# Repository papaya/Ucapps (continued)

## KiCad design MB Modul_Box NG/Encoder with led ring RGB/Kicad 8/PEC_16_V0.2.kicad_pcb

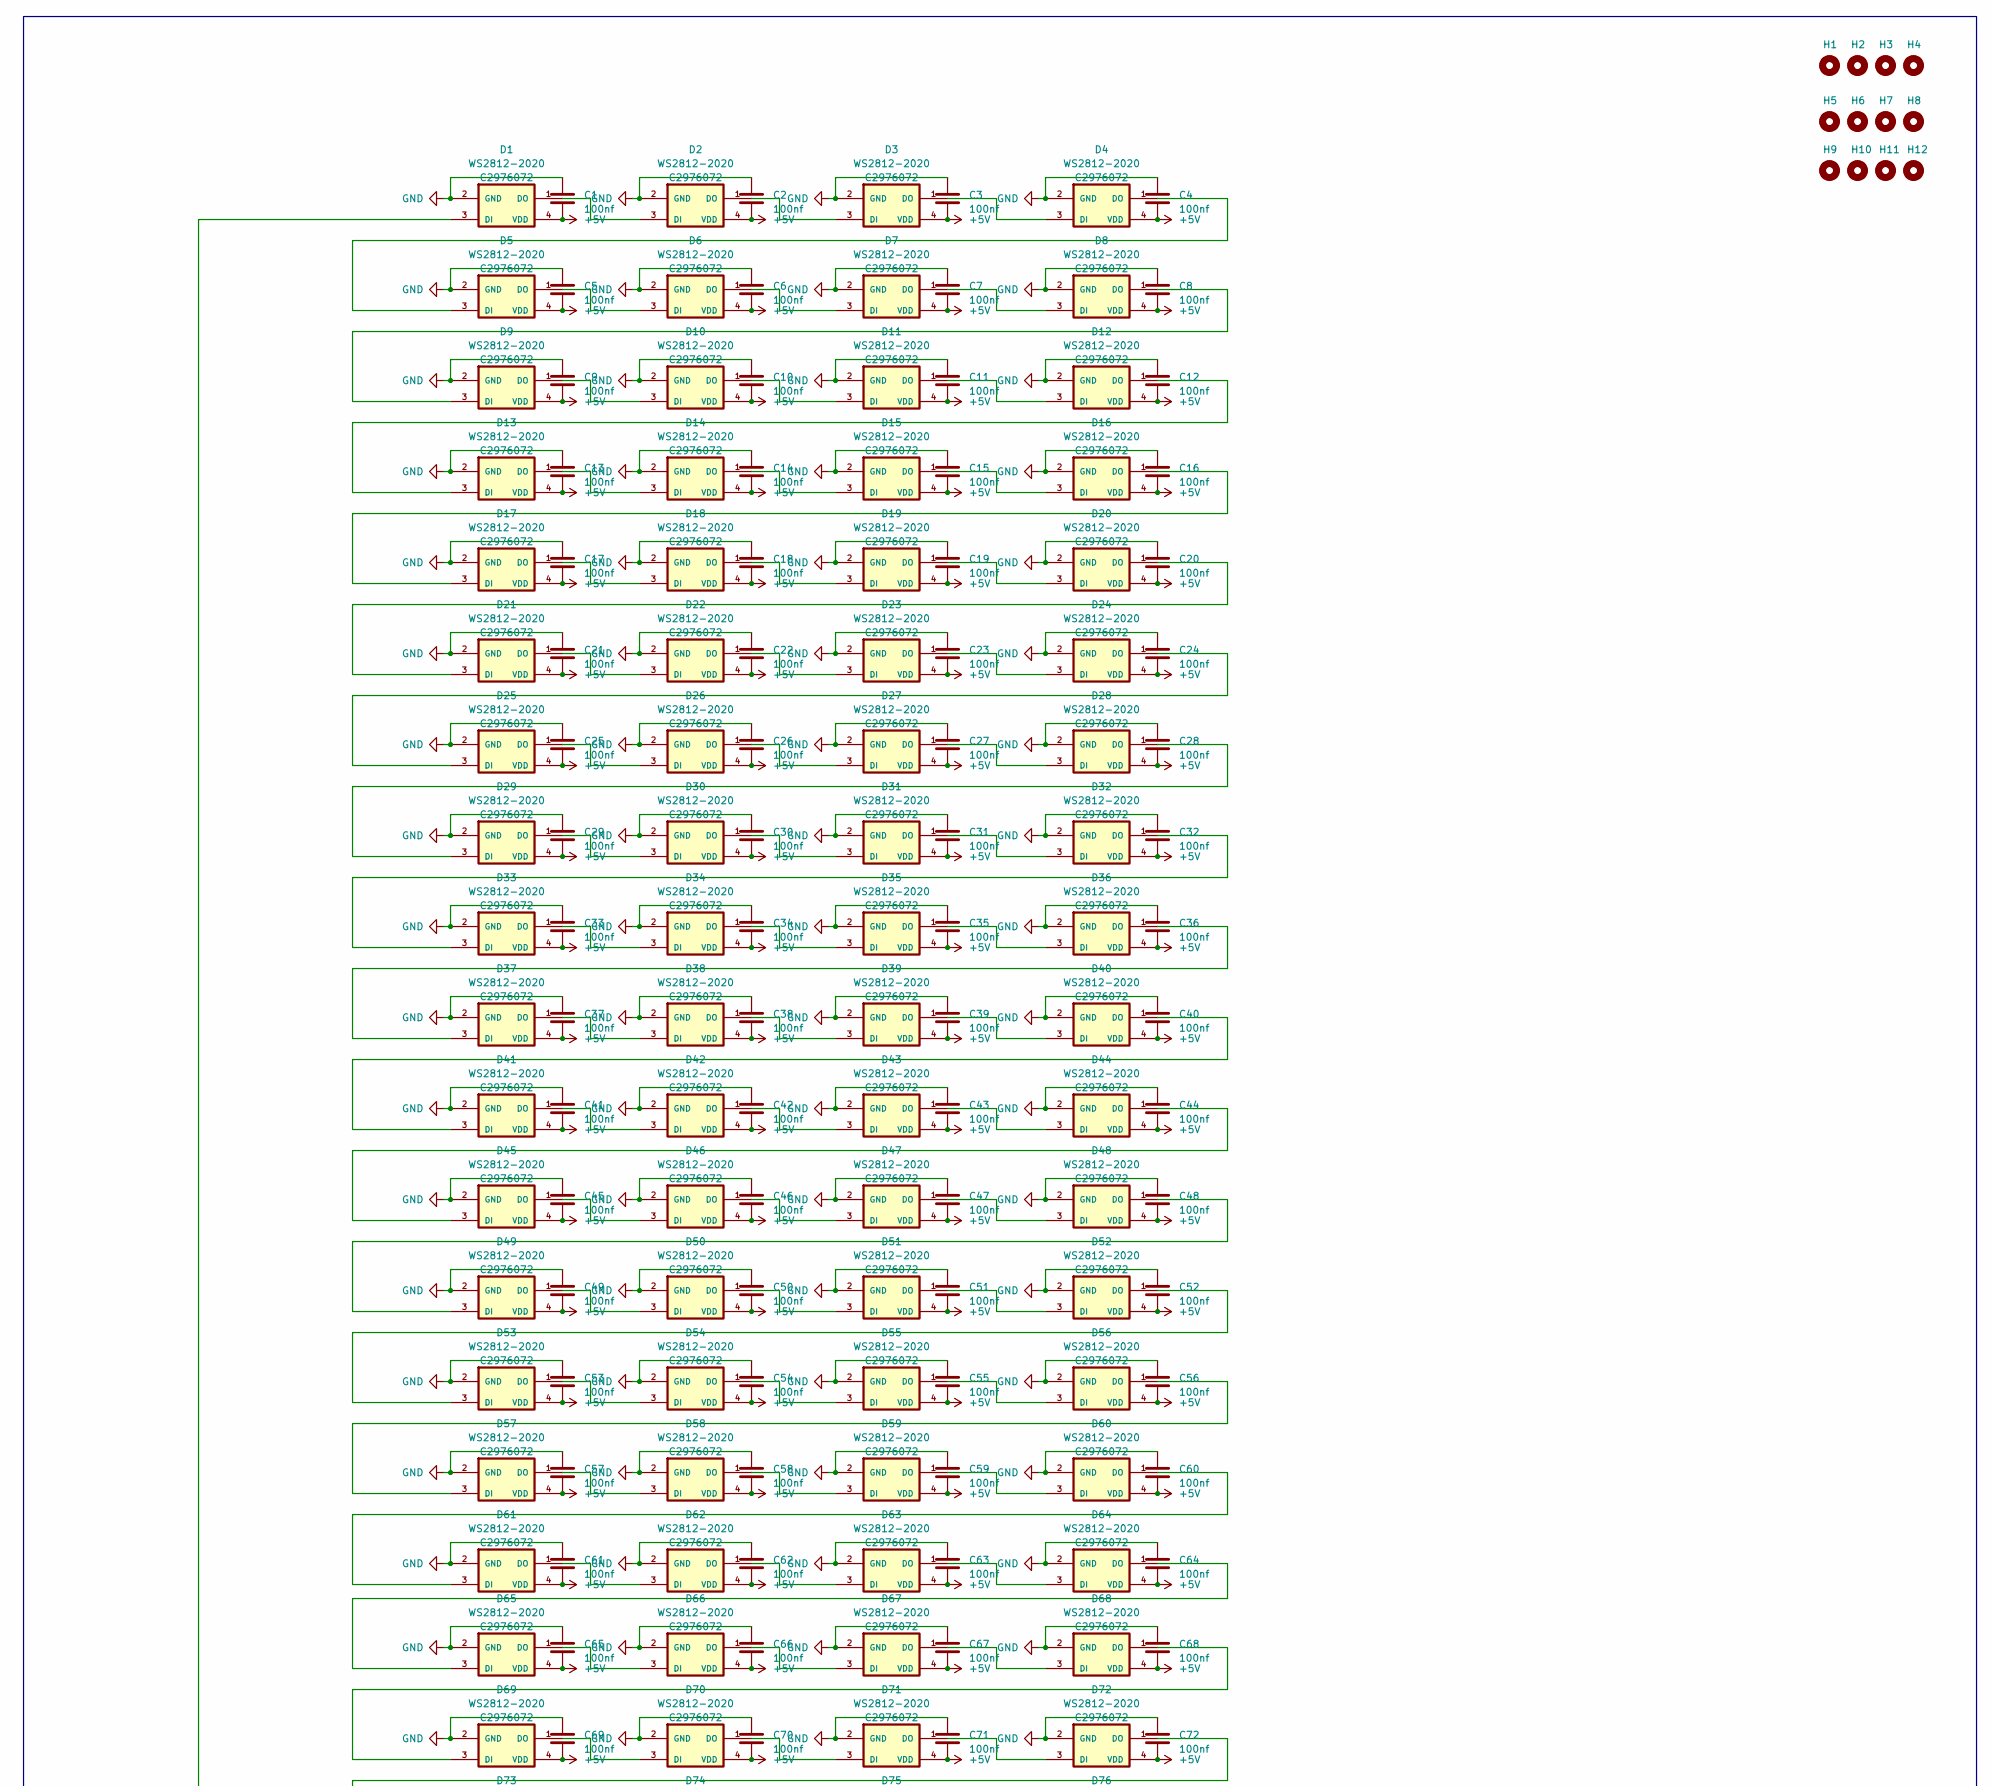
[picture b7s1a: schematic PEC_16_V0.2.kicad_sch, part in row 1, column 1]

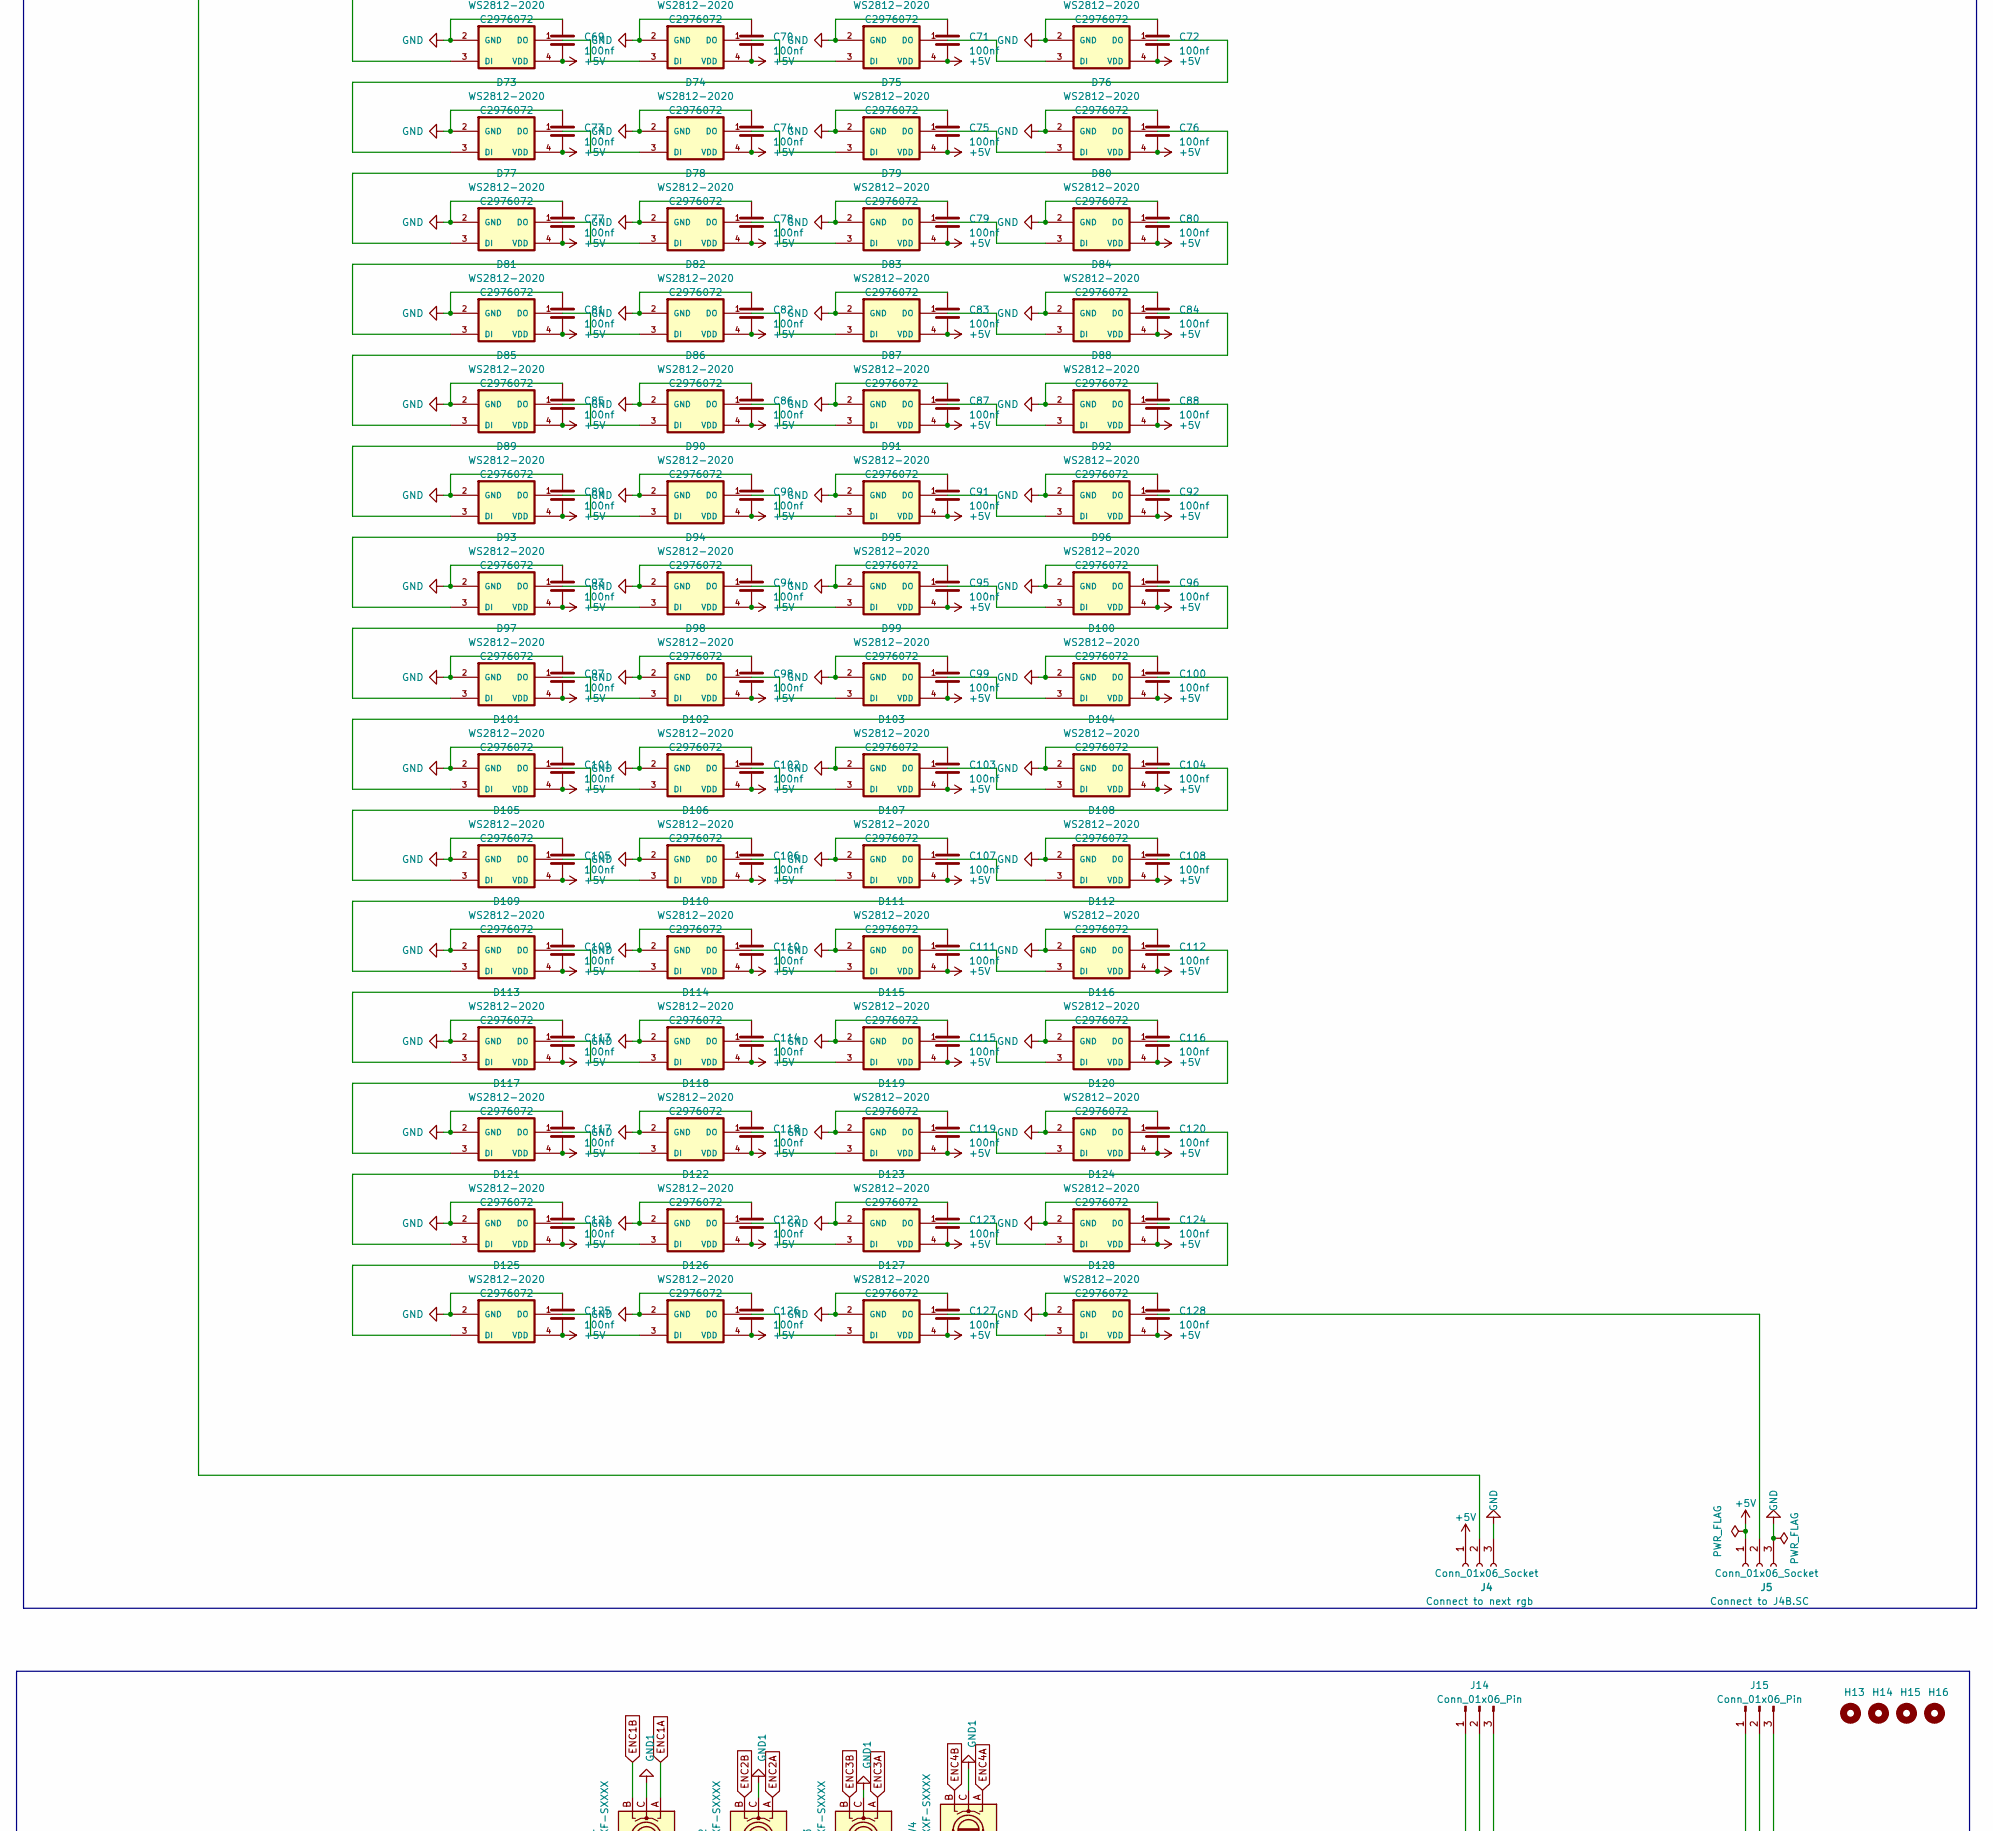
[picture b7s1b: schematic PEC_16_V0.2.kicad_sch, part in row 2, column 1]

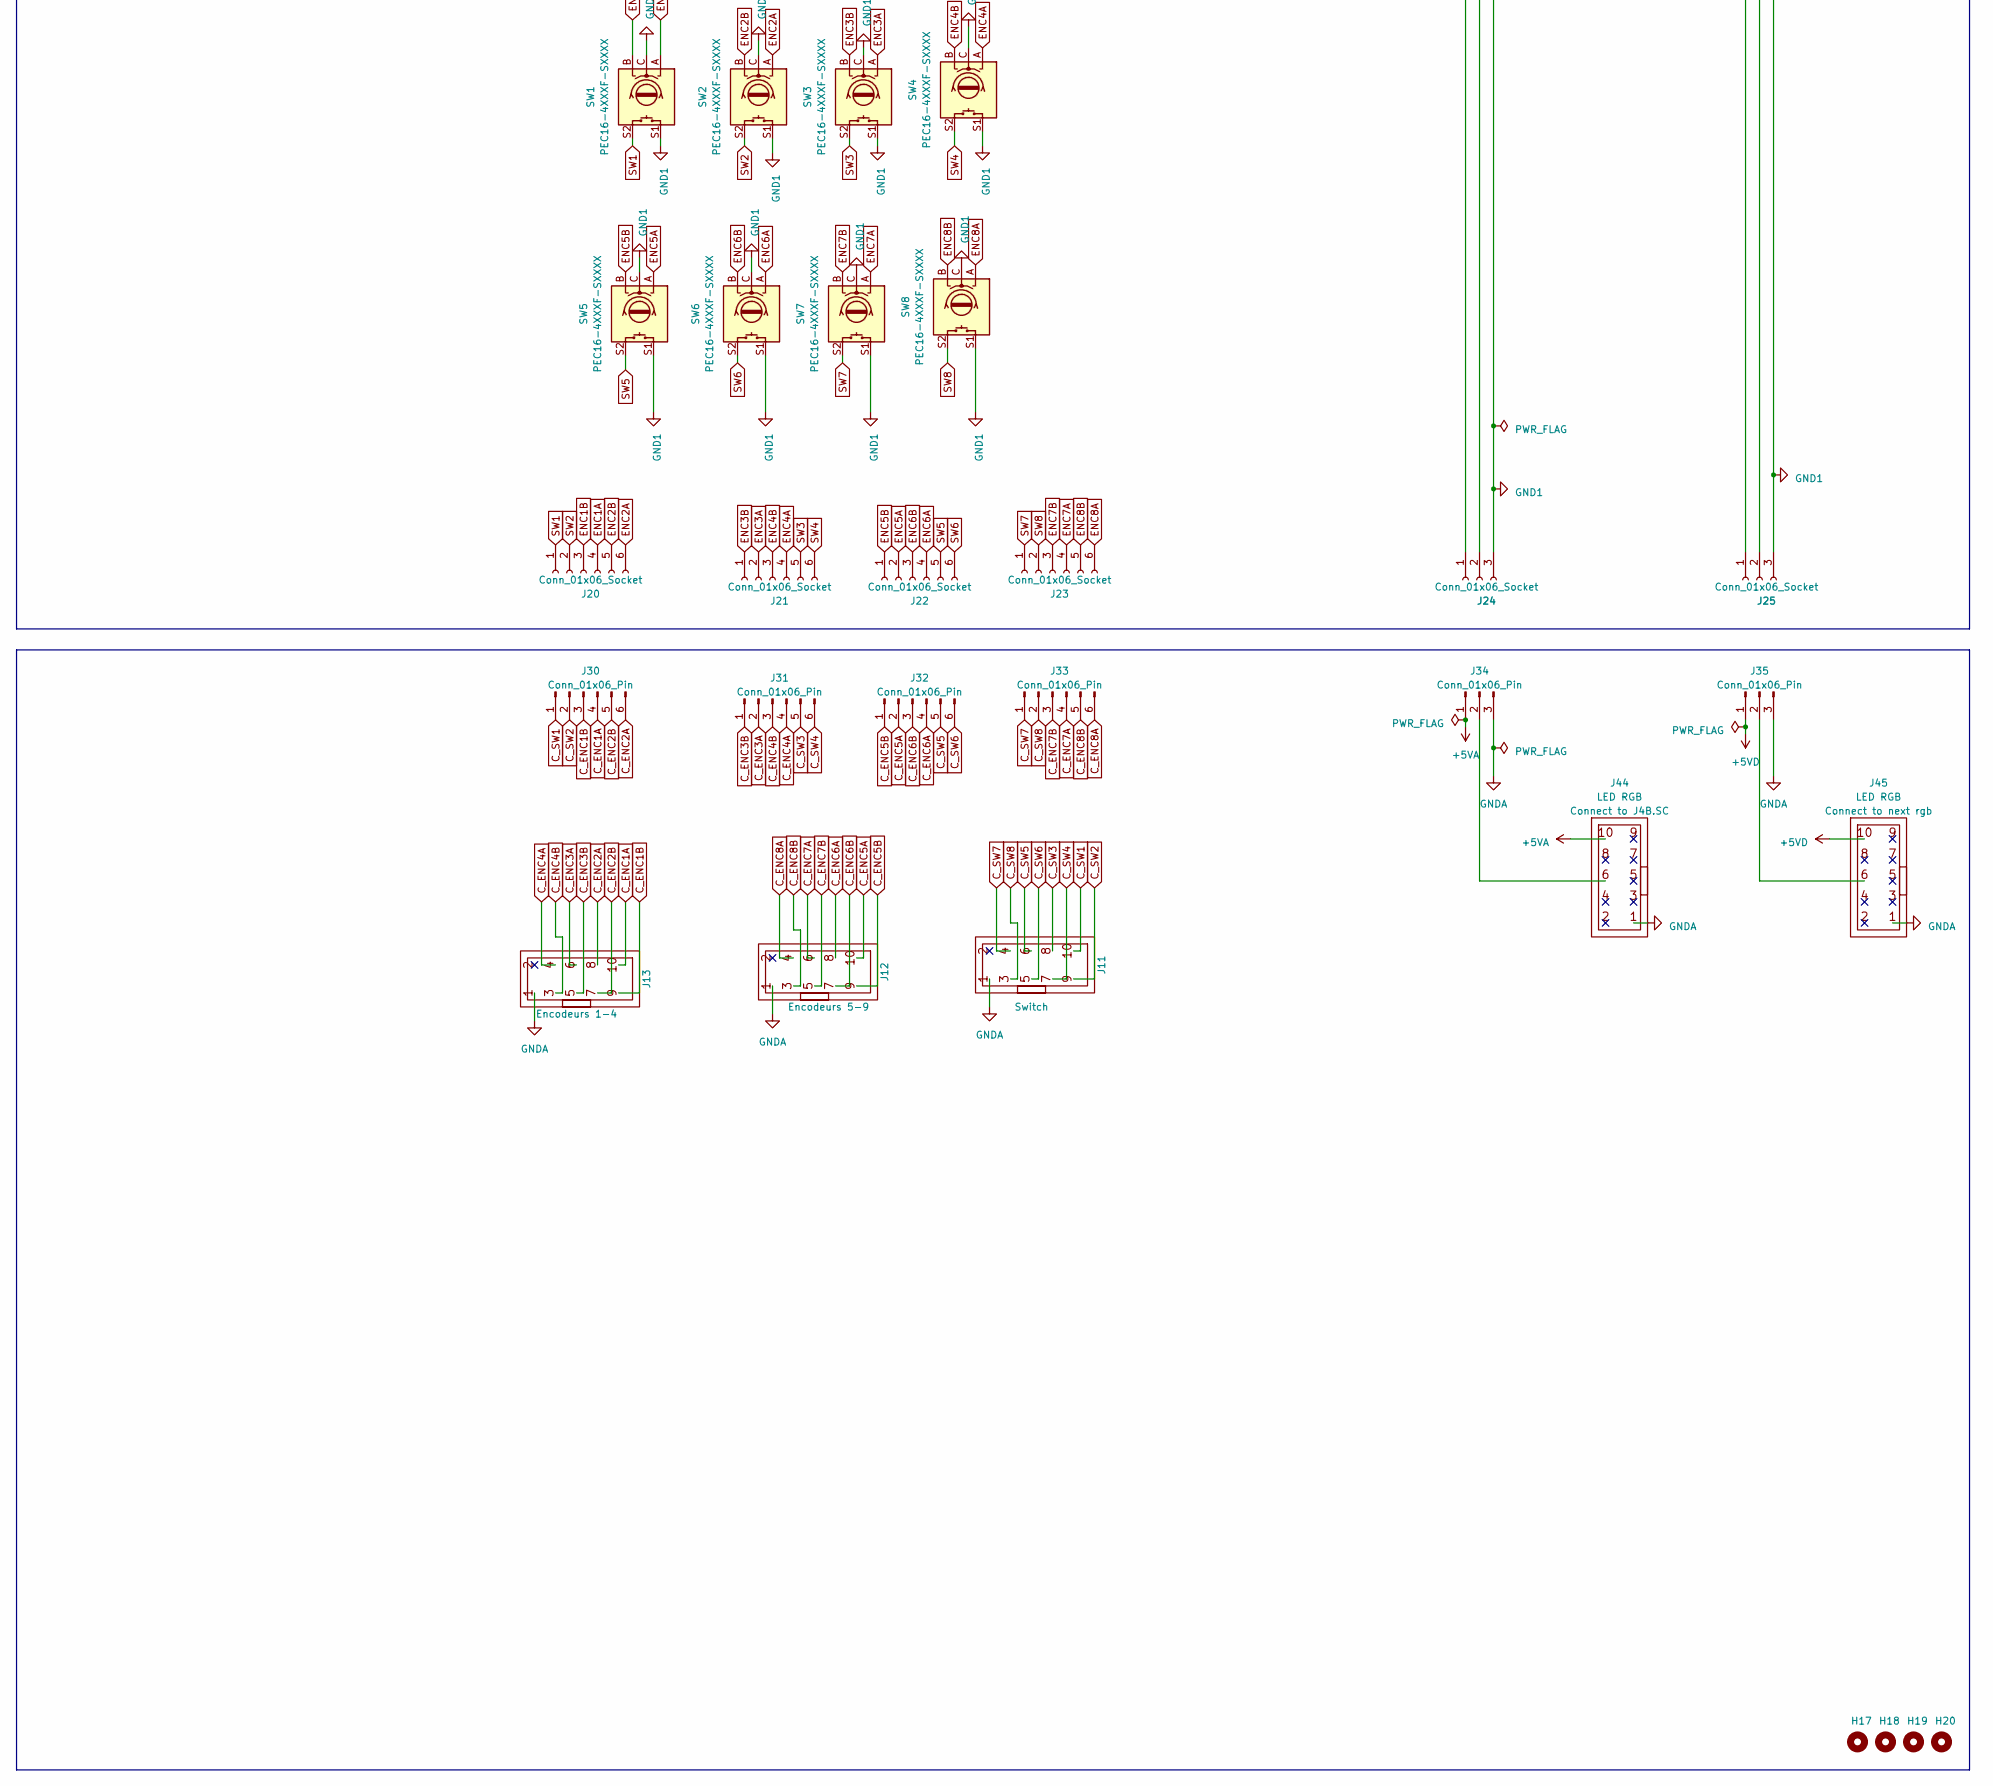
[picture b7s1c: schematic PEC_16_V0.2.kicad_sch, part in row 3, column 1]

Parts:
C1, C2, C3, C4, C5, C6, C7, C8, C9, C10, C11, C12, C13, C14, C15, C16, C17, C18, C19, C20, C21, C22, C23, C24, C25, C26, C27, C28, C29, C30, C31, C32, C33, C34, C35, C36, C37, C38, C39, C40, C41, C42, C43, C44, C45, C46, C47, C48, C49, C50, C51, C52, C53, C54, C55, C56, C57, C58, C59, C60, C61, C62, C63, C64, C65, C66, C67, C68, C69, C70, C71, C72, C73, C74, C75, C76, C77, C78, C79, C80, C81, C82, C83, C84, C85, C86, C87, C88, C89, C90, C91, C92, C93, C94, C95, C96, C97, C98, C99, C100, C101, C102, C103, C104, C105, C106, C107, C108, C109, C110, C111, C112, C113, C114, C115, C116, C117, C118, C119, C120, C121, C122, C123, C124, C125, C126, C127, C128: 100nf; CAPC1005X55N; JLCPCB Part # C1525
D1, D2, D3, D4, D5, D6, D7, D8, D9, D10, D11, D12, D13, D14, D15, D16, D17, D18, D19, D20, D21, D22, D23, D24, D25, D26, D27, D28, D29, D30, D31, D32, D33, D34, D35, D36, D37, D38, D39, D40, D41, D42, D43, D44, D45, D46, D47, D48, D49, D50, D51, D52, D53, D54, D55, D56, D57, D58, D59, D60, D61, D62, D63, D64, D65, D66, D67, D68, D69, D70, D71, D72, D73, D74, D75, D76, D77, D78, D79, D80, D81, D82, D83, D84, D85, D86, D87, D88, D89, D90, D91, D92, D93, D94, D95, D96, D97, D98, D99, D100, D101, D102, D103, D104, D105, D106, D107, D108, D109, D110, D111, D112, D113, D114, D115, D116, D117, D118, D119, D120, D121, D122, D123, D124, D125, D126, D127, D128: WS2812-2020; LED_WS2812B-2020_PLCC4_2.0x2.0mm; JLCPCB Part # C2976072
H1, H2, H3, H4, H13, H14, H15, H16, H17, H18, H19, H20: MountingHole; MountingHole_3.2mm_M3
H5, H6, H7, H8, H9, H10, H11, H12: MountingHole; Hole_9.5mm
J4, J5, J24, J25: Conn_01x06_Socket; PinSocket_1x03_P2.54mm_Vertical
J11, J12, J13: sin_in; IDC-Header_2x05_P2.54mm_Vertical_ksr_dIN
J14, J15, J34, J35: Conn_01x06_Pin; PinHeader_1x03_P2.54mm_Vertical
J20, J21, J22, J23: Conn_01x06_Socket; PinSocket_1x06_P2.54mm_Vertical
J30, J31, J32, J33: Conn_01x06_Pin; PinHeader_1x06_P2.54mm_Vertical
J44, J45: IDC-Header_2x05_P2.54mm_Vertical
SW1, SW2, SW3, SW4, SW5, SW6, SW7, SW8: PEC16-4XXXF-SXXXX; PEC164120FS0012

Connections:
+5V: C1.2, C2.2, C3.2, C4.2, C5.2, C6.2, C7.2, C8.2, C9.2, C10.2, C11.2, C12.2, C13.2, C14.2, C15.2, C16.2, C17.2, C18.2, C19.2, C20.2, C21.2, C22.2, C23.2, C24.2, C25.2, C26.2, C27.2, C28.2, C29.2, C30.2, C31.2, C32.2, C33.2, C34.2, C35.2, C36.2, C37.2, C38.2, C39.2, C40.2, C41.2, C42.2, C43.2, C44.2, C45.2, C46.2, C47.2, C48.2, C49.2, C50.2, C51.2, C52.2, C53.2, C54.2, C55.2, C56.2, C57.2, C58.2, C59.2, C60.2, C61.2, C62.2, C63.2, C64.2, C65.2, C66.2, C67.2, C68.2, C69.2, C70.2, C71.2, C72.2, C73.2, C74.2, C75.2, C76.2, C77.2, C78.2, C79.2, C80.2, C81.2, C82.2, C83.2, C84.2, C85.2, C86.2, C87.2, C88.2, C89.2, C90.2, C91.2, C92.2, C93.2, C94.2, C95.2, C96.2, C97.2, C98.2, C99.2, C100.2, C101.2, C102.2, C103.2, C104.2, C105.2, C106.2, C107.2, C108.2, C109.2, C110.2, C111.2, C112.2, C113.2, C114.2, C115.2, C116.2, C117.2, C118.2, C119.2, C120.2, C121.2, C122.2, C123.2, C124.2, C125.2, C126.2, C127.2, C128.2, D1.4 (VDD), D2.4 (VDD), D3.4 (VDD), D4.4 (VDD), D5.4 (VDD), D6.4 (VDD), D7.4 (VDD), D8.4 (VDD), D9.4 (VDD), D10.4 (VDD), D11.4 (VDD), D12.4 (VDD), D13.4 (VDD), D14.4 (VDD), D15.4 (VDD), D16.4 (VDD), D17.4 (VDD), D18.4 (VDD), D19.4 (VDD), D20.4 (VDD), D21.4 (VDD), D22.4 (VDD), D23.4 (VDD), D24.4 (VDD), D25.4 (VDD), D26.4 (VDD), D27.4 (VDD), D28.4 (VDD), D29.4 (VDD), D30.4 (VDD), D31.4 (VDD), D32.4 (VDD), D33.4 (VDD), D34.4 (VDD), D35.4 (VDD), D36.4 (VDD), D37.4 (VDD), D38.4 (VDD), D39.4 (VDD), D40.4 (VDD), D41.4 (VDD), D42.4 (VDD), D43.4 (VDD), D44.4 (VDD), D45.4 (VDD), D46.4 (VDD), D47.4 (VDD), D48.4 (VDD), D49.4 (VDD), D50.4 (VDD), D51.4 (VDD), D52.4 (VDD), D53.4 (VDD), D54.4 (VDD), D55.4 (VDD), D56.4 (VDD), D57.4 (VDD), D58.4 (VDD), D59.4 (VDD), D60.4 (VDD), D61.4 (VDD), D62.4 (VDD), D63.4 (VDD), D64.4 (VDD), D65.4 (VDD), D66.4 (VDD), D67.4 (VDD), D68.4 (VDD), D69.4 (VDD), D70.4 (VDD), D71.4 (VDD), D72.4 (VDD), D73.4 (VDD), D74.4 (VDD), D75.4 (VDD), D76.4 (VDD), D77.4 (VDD), D78.4 (VDD), D79.4 (VDD), D80.4 (VDD), D81.4 (VDD), D82.4 (VDD), D83.4 (VDD), D84.4 (VDD), D85.4 (VDD), D86.4 (VDD), D87.4 (VDD), D88.4 (VDD), D89.4 (VDD), D90.4 (VDD), D91.4 (VDD), D92.4 (VDD), D93.4 (VDD), D94.4 (VDD), D95.4 (VDD), D96.4 (VDD), D97.4 (VDD), D98.4 (VDD), D99.4 (VDD), D100.4 (VDD), D101.4 (VDD), D102.4 (VDD), D103.4 (VDD), D104.4 (VDD), D105.4 (VDD), D106.4 (VDD), D107.4 (VDD), D108.4 (VDD), D109.4 (VDD), D110.4 (VDD), D111.4 (VDD), D112.4 (VDD), D113.4 (VDD), D114.4 (VDD), D115.4 (VDD), D116.4 (VDD), D117.4 (VDD), D118.4 (VDD), D119.4 (VDD), D120.4 (VDD), D121.4 (VDD), D122.4 (VDD), D123.4 (VDD), D124.4 (VDD), D125.4 (VDD), D126.4 (VDD), D127.4 (VDD), D128.4 (VDD), J4.1, J5.1
+5VA: J34.1, J44.10
+5VD: J35.1, J45.10
C_ENC1A: J13.10, J30.4
C_ENC1B: J13.9, J30.3
C_ENC2A: J13.8, J30.6
C_ENC2B: J13.7, J30.5
C_ENC3A: J13.6, J31.2
C_ENC3B: J13.5, J31.1
C_ENC4A: J13.4, J31.4
C_ENC4B: J13.3, J31.3
C_ENC5A: J12.10, J32.2
C_ENC5B: J12.9, J32.1
C_ENC6A: J12.8, J32.4
C_ENC6B: J12.7, J32.3
C_ENC7A: J12.6, J33.4
C_ENC7B: J12.5, J33.3
C_ENC8A: J12.4, J33.6
C_ENC8B: J12.3, J33.5
C_SW1: J11.10, J30.1
C_SW2: J11.9, J30.2
C_SW3: J11.8, J31.5
C_SW4: J11.7, J31.6
C_SW5: J11.6, J32.5
C_SW6: J11.5, J32.6
C_SW7: J11.4, J33.1
C_SW8: J11.3, J33.2
ENC1A: J20.4, SW1.A
ENC1B: J20.3, SW1.B
ENC2A: J20.6, SW2.A
ENC2B: J20.5, SW2.B
ENC3A: J21.2, SW3.A
ENC3B: J21.1, SW3.B
ENC4A: J21.4, SW4.A
ENC4B: J21.3, SW4.B
ENC5A: J22.2, SW5.A
ENC5B: J22.1, SW5.B
ENC6A: J22.4, SW6.A
ENC6B: J22.3, SW6.B
ENC7A: J23.4, SW7.A
ENC7B: J23.3, SW7.B
ENC8A: J23.6, SW8.A
ENC8B: J23.5, SW8.B
GND: C1.1, C2.1, C3.1, C4.1, C5.1, C6.1, C7.1, C8.1, C9.1, C10.1, C11.1, C12.1, C13.1, C14.1, C15.1, C16.1, C17.1, C18.1, C19.1, C20.1, C21.1, C22.1, C23.1, C24.1, C25.1, C26.1, C27.1, C28.1, C29.1, C30.1, C31.1, C32.1, C33.1, C34.1, C35.1, C36.1, C37.1, C38.1, C39.1, C40.1, C41.1, C42.1, C43.1, C44.1, C45.1, C46.1, C47.1, C48.1, C49.1, C50.1, C51.1, C52.1, C53.1, C54.1, C55.1, C56.1, C57.1, C58.1, C59.1, C60.1, C61.1, C62.1, C63.1, C64.1, C65.1, C66.1, C67.1, C68.1, C69.1, C70.1, C71.1, C72.1, C73.1, C74.1, C75.1, C76.1, C77.1, C78.1, C79.1, C80.1, C81.1, C82.1, C83.1, C84.1, C85.1, C86.1, C87.1, C88.1, C89.1, C90.1, C91.1, C92.1, C93.1, C94.1, C95.1, C96.1, C97.1, C98.1, C99.1, C100.1, C101.1, C102.1, C103.1, C104.1, C105.1, C106.1, C107.1, C108.1, C109.1, C110.1, C111.1, C112.1, C113.1, C114.1, C115.1, C116.1, C117.1, C118.1, C119.1, C120.1, C121.1, C122.1, C123.1, C124.1, C125.1, C126.1, C127.1, C128.1, D1.2 (GND), D2.2 (GND), D3.2 (GND), D4.2 (GND), D5.2 (GND), D6.2 (GND), D7.2 (GND), D8.2 (GND), D9.2 (GND), D10.2 (GND), D11.2 (GND), D12.2 (GND), D13.2 (GND), D14.2 (GND), D15.2 (GND), D16.2 (GND), D17.2 (GND), D18.2 (GND), D19.2 (GND), D20.2 (GND), D21.2 (GND), D22.2 (GND), D23.2 (GND), D24.2 (GND), D25.2 (GND), D26.2 (GND), D27.2 (GND), D28.2 (GND), D29.2 (GND), D30.2 (GND), D31.2 (GND), D32.2 (GND), D33.2 (GND), D34.2 (GND), D35.2 (GND), D36.2 (GND), D37.2 (GND), D38.2 (GND), D39.2 (GND), D40.2 (GND), D41.2 (GND), D42.2 (GND), D43.2 (GND), D44.2 (GND), D45.2 (GND), D46.2 (GND), D47.2 (GND), D48.2 (GND), D49.2 (GND), D50.2 (GND), D51.2 (GND), D52.2 (GND), D53.2 (GND), D54.2 (GND), D55.2 (GND), D56.2 (GND), D57.2 (GND), D58.2 (GND), D59.2 (GND), D60.2 (GND), D61.2 (GND), D62.2 (GND), D63.2 (GND), D64.2 (GND), D65.2 (GND), D66.2 (GND), D67.2 (GND), D68.2 (GND), D69.2 (GND), D70.2 (GND), D71.2 (GND), D72.2 (GND), D73.2 (GND), D74.2 (GND), D75.2 (GND), D76.2 (GND), D77.2 (GND), D78.2 (GND), D79.2 (GND), D80.2 (GND), D81.2 (GND), D82.2 (GND), D83.2 (GND), D84.2 (GND), D85.2 (GND), D86.2 (GND), D87.2 (GND), D88.2 (GND), D89.2 (GND), D90.2 (GND), D91.2 (GND), D92.2 (GND), D93.2 (GND), D94.2 (GND), D95.2 (GND), D96.2 (GND), D97.2 (GND), D98.2 (GND), D99.2 (GND), D100.2 (GND), D101.2 (GND), D102.2 (GND), D103.2 (GND), D104.2 (GND), D105.2 (GND), D106.2 (GND), D107.2 (GND), D108.2 (GND), D109.2 (GND), D110.2 (GND), D111.2 (GND), D112.2 (GND), D113.2 (GND), D114.2 (GND), D115.2 (GND), D116.2 (GND), D117.2 (GND), D118.2 (GND), D119.2 (GND), D120.2 (GND), D121.2 (GND), D122.2 (GND), D123.2 (GND), D124.2 (GND), D125.2 (GND), D126.2 (GND), D127.2 (GND), D128.2 (GND), J4.3, J5.3
GND1: J14.3, J15.3, J24.3, J25.3, SW1.C, SW1.S1, SW2.C, SW2.S1, SW3.C, SW3.S1, SW4.C, SW4.S1, SW5.C, SW5.S1, SW6.C, SW6.S1, SW7.C, SW7.S1, SW8.C, SW8.S1
GNDA: J11.1, J12.1, J13.1, J34.3, J35.3, J44.1, J45.1
unnamed: D1.3 (DI), J4.2
unnamed: D1.1 (DO), D2.3 (DI)
unnamed: D2.1 (DO), D3.3 (DI)
unnamed: D3.1 (DO), D4.3 (DI)
unnamed: D4.1 (DO), D5.3 (DI)
unnamed: D5.1 (DO), D6.3 (DI)
unnamed: D6.1 (DO), D7.3 (DI)
unnamed: D7.1 (DO), D8.3 (DI)
unnamed: D8.1 (DO), D9.3 (DI)
unnamed: D9.1 (DO), D10.3 (DI)
unnamed: D10.1 (DO), D11.3 (DI)
unnamed: D11.1 (DO), D12.3 (DI)
unnamed: D12.1 (DO), D13.3 (DI)
unnamed: D13.1 (DO), D14.3 (DI)
unnamed: D14.1 (DO), D15.3 (DI)
unnamed: D15.1 (DO), D16.3 (DI)
unnamed: D16.1 (DO), D17.3 (DI)
unnamed: D17.1 (DO), D18.3 (DI)
unnamed: D18.1 (DO), D19.3 (DI)
unnamed: D19.1 (DO), D20.3 (DI)
unnamed: D20.1 (DO), D21.3 (DI)
unnamed: D21.1 (DO), D22.3 (DI)
unnamed: D22.1 (DO), D23.3 (DI)
unnamed: D23.1 (DO), D24.3 (DI)
unnamed: D24.1 (DO), D25.3 (DI)
unnamed: D25.1 (DO), D26.3 (DI)
unnamed: D26.1 (DO), D27.3 (DI)
unnamed: D27.1 (DO), D28.3 (DI)
unnamed: D28.1 (DO), D29.3 (DI)
unnamed: D29.1 (DO), D30.3 (DI)
unnamed: D30.1 (DO), D31.3 (DI)
unnamed: D31.1 (DO), D32.3 (DI)
unnamed: D32.1 (DO), D33.3 (DI)
unnamed: D33.1 (DO), D34.3 (DI)
unnamed: D34.1 (DO), D35.3 (DI)
unnamed: D35.1 (DO), D36.3 (DI)
unnamed: D36.1 (DO), D37.3 (DI)
unnamed: D37.1 (DO), D38.3 (DI)
unnamed: D38.1 (DO), D39.3 (DI)
unnamed: D39.1 (DO), D40.3 (DI)
unnamed: D40.1 (DO), D41.3 (DI)
unnamed: D41.1 (DO), D42.3 (DI)
unnamed: D42.1 (DO), D43.3 (DI)
unnamed: D43.1 (DO), D44.3 (DI)
unnamed: D44.1 (DO), D45.3 (DI)
unnamed: D45.1 (DO), D46.3 (DI)
unnamed: D46.1 (DO), D47.3 (DI)
unnamed: D47.1 (DO), D48.3 (DI)
unnamed: D48.1 (DO), D49.3 (DI)
unnamed: D49.1 (DO), D50.3 (DI)
unnamed: D50.1 (DO), D51.3 (DI)
unnamed: D51.1 (DO), D52.3 (DI)
unnamed: D52.1 (DO), D53.3 (DI)
unnamed: D53.1 (DO), D54.3 (DI)
unnamed: D54.1 (DO), D55.3 (DI)
unnamed: D55.1 (DO), D56.3 (DI)
unnamed: D56.1 (DO), D57.3 (DI)
unnamed: D57.1 (DO), D58.3 (DI)
unnamed: D58.1 (DO), D59.3 (DI)
unnamed: D59.1 (DO), D60.3 (DI)
unnamed: D60.1 (DO), D61.3 (DI)
unnamed: D61.1 (DO), D62.3 (DI)
unnamed: D62.1 (DO), D63.3 (DI)
unnamed: D63.1 (DO), D64.3 (DI)
unnamed: D64.1 (DO), D65.3 (DI)
unnamed: D65.1 (DO), D66.3 (DI)
unnamed: D66.1 (DO), D67.3 (DI)
unnamed: D67.1 (DO), D68.3 (DI)
unnamed: D68.1 (DO), D69.3 (DI)
unnamed: D69.1 (DO), D70.3 (DI)
unnamed: D70.1 (DO), D71.3 (DI)
unnamed: D71.1 (DO), D72.3 (DI)
unnamed: D72.1 (DO), D73.3 (DI)
unnamed: D73.1 (DO), D74.3 (DI)
unnamed: D74.1 (DO), D75.3 (DI)
unnamed: D75.1 (DO), D76.3 (DI)
unnamed: D76.1 (DO), D77.3 (DI)
unnamed: D77.1 (DO), D78.3 (DI)
unnamed: D78.1 (DO), D79.3 (DI)
unnamed: D79.1 (DO), D80.3 (DI)
unnamed: D80.1 (DO), D81.3 (DI)
unnamed: D81.1 (DO), D82.3 (DI)
unnamed: D82.1 (DO), D83.3 (DI)
unnamed: D83.1 (DO), D84.3 (DI)
unnamed: D84.1 (DO), D85.3 (DI)
unnamed: D85.1 (DO), D86.3 (DI)
unnamed: D86.1 (DO), D87.3 (DI)
unnamed: D87.1 (DO), D88.3 (DI)
unnamed: D88.1 (DO), D89.3 (DI)
unnamed: D89.1 (DO), D90.3 (DI)
unnamed: D90.1 (DO), D91.3 (DI)
unnamed: D91.1 (DO), D92.3 (DI)
unnamed: D92.1 (DO), D93.3 (DI)
unnamed: D93.1 (DO), D94.3 (DI)
unnamed: D94.1 (DO), D95.3 (DI)
unnamed: D95.1 (DO), D96.3 (DI)
unnamed: D96.1 (DO), D97.3 (DI)
unnamed: D97.1 (DO), D98.3 (DI)
unnamed: D98.1 (DO), D99.3 (DI)
unnamed: D99.1 (DO), D100.3 (DI)
unnamed: D100.1 (DO), D101.3 (DI)
unnamed: D101.1 (DO), D102.3 (DI)
unnamed: D102.1 (DO), D103.3 (DI)
unnamed: D103.1 (DO), D104.3 (DI)
unnamed: D104.1 (DO), D105.3 (DI)
unnamed: D105.1 (DO), D106.3 (DI)
unnamed: D106.1 (DO), D107.3 (DI)
unnamed: D107.1 (DO), D108.3 (DI)
unnamed: D108.1 (DO), D109.3 (DI)
unnamed: D109.1 (DO), D110.3 (DI)
unnamed: D110.1 (DO), D111.3 (DI)
unnamed: D111.1 (DO), D112.3 (DI)
unnamed: D112.1 (DO), D113.3 (DI)
unnamed: D113.1 (DO), D114.3 (DI)
unnamed: D114.1 (DO), D115.3 (DI)
unnamed: D115.1 (DO), D116.3 (DI)
unnamed: D116.1 (DO), D117.3 (DI)
unnamed: D117.1 (DO), D118.3 (DI)
unnamed: D118.1 (DO), D119.3 (DI)
unnamed: D119.1 (DO), D120.3 (DI)
unnamed: D120.1 (DO), D121.3 (DI)
unnamed: D121.1 (DO), D122.3 (DI)
unnamed: D122.1 (DO), D123.3 (DI)
unnamed: D123.1 (DO), D124.3 (DI)
unnamed: D124.1 (DO), D125.3 (DI)
unnamed: D125.1 (DO), D126.3 (DI)
unnamed: D126.1 (DO), D127.3 (DI)
unnamed: D127.1 (DO), D128.3 (DI)
unnamed: D128.1 (DO), J5.2
unnamed: J14.1, J24.1
unnamed: J14.2, J24.2
unnamed: J15.1, J25.1
unnamed: J15.2, J25.2
unnamed: J34.2, J44.6
unnamed: J35.2, J45.6
SW1: J20.1, SW1.S2
SW2: J20.2, SW2.S2
SW3: J21.5, SW3.S2
SW4: J21.6, SW4.S2
SW5: J22.5, SW5.S2
SW6: J22.6, SW6.S2
SW7: J23.1, SW7.S2
SW8: J23.2, SW8.S2

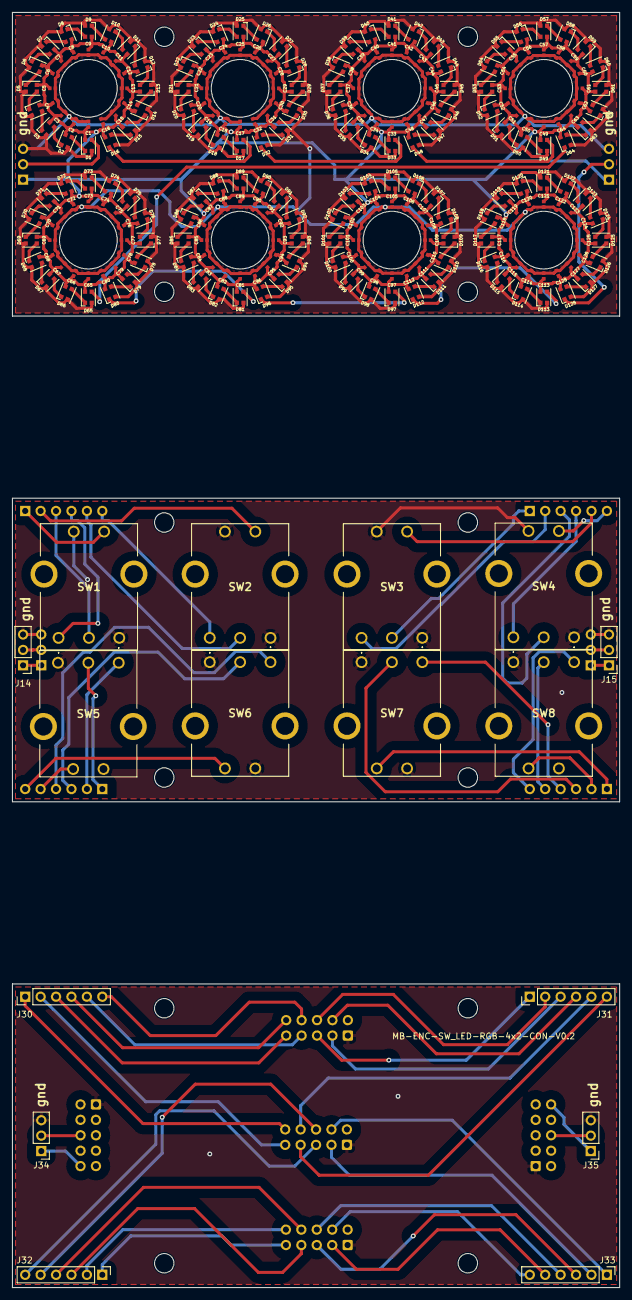
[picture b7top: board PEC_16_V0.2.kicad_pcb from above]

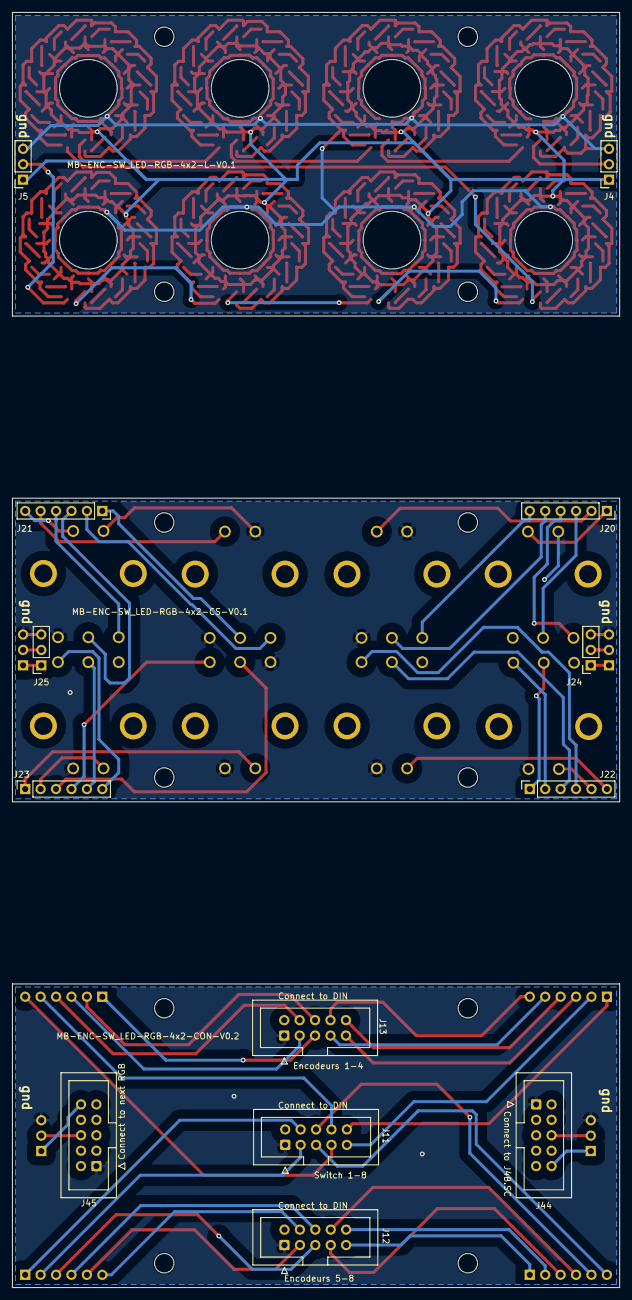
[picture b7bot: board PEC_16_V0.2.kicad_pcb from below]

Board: 2 copper layers, 100.0 x 50.0 mm, 305 parts (13 on the bottom side), 189 nets.

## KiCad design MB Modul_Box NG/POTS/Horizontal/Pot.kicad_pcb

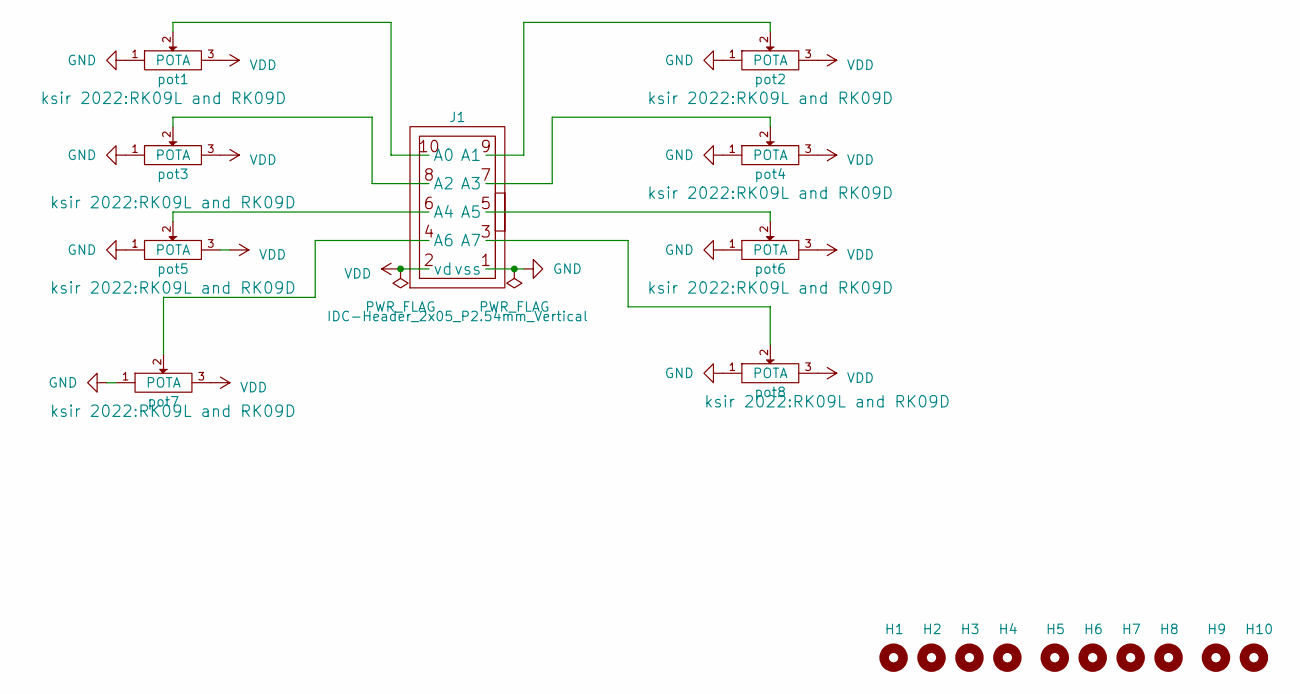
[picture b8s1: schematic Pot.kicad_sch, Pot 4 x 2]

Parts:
H1, H2, H3, H4, H5, H6, H7, H8, H9, H10: MountingHole; MountingHole_3.2mm_M3
J1: IDC-Header_2x05_P2.54mm_Vertical
pot1, pot2, pot3, pot4, pot5, pot6, pot7, pot8: POTA; RK09L and RK09D

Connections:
GND: J1.1 (vss), pot1.1 (vss_masse), pot2.1 (vss_masse), pot3.1 (vss_masse), pot4.1 (vss_masse), pot5.1 (vss_masse), pot6.1 (vss_masse), pot7.1 (vss_masse), pot8.1 (vss_masse)
unnamed: J1.10 (A0), pot1.2
unnamed: J1.9 (A1), pot2.2
unnamed: J1.8 (A2), pot3.2
unnamed: J1.7 (A3), pot4.2
unnamed: J1.6 (A4), pot5.2
unnamed: J1.5 (A5), pot6.2
unnamed: J1.4 (A6), pot7.2
unnamed: J1.3 (A7), pot8.2
VDD: J1.2 (vd), pot1.3 (vd), pot2.3 (vd), pot3.3 (vd), pot4.3 (vd), pot5.3 (vd), pot6.3 (vd), pot7.3 (vd), pot8.3 (vd)

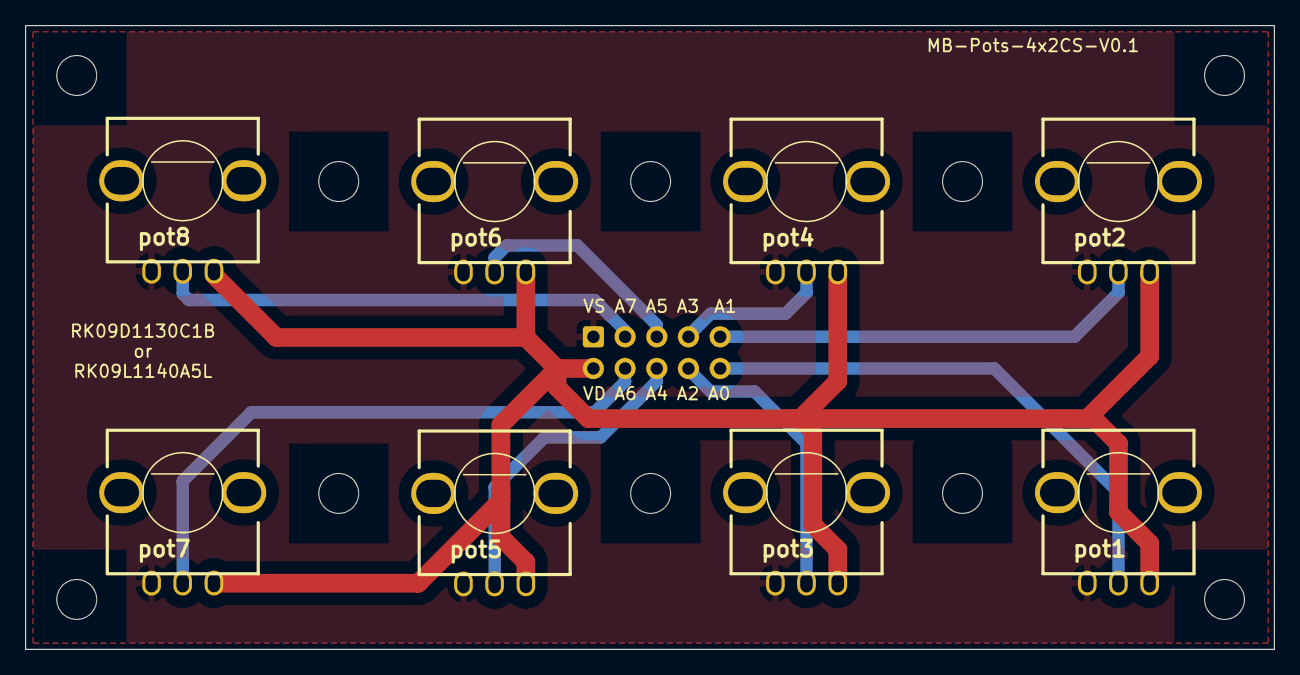
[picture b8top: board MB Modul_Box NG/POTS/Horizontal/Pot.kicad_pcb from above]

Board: 2 copper layers, 100.1 x 50.0 mm, 19 parts (1 on the bottom side), 10 nets.
